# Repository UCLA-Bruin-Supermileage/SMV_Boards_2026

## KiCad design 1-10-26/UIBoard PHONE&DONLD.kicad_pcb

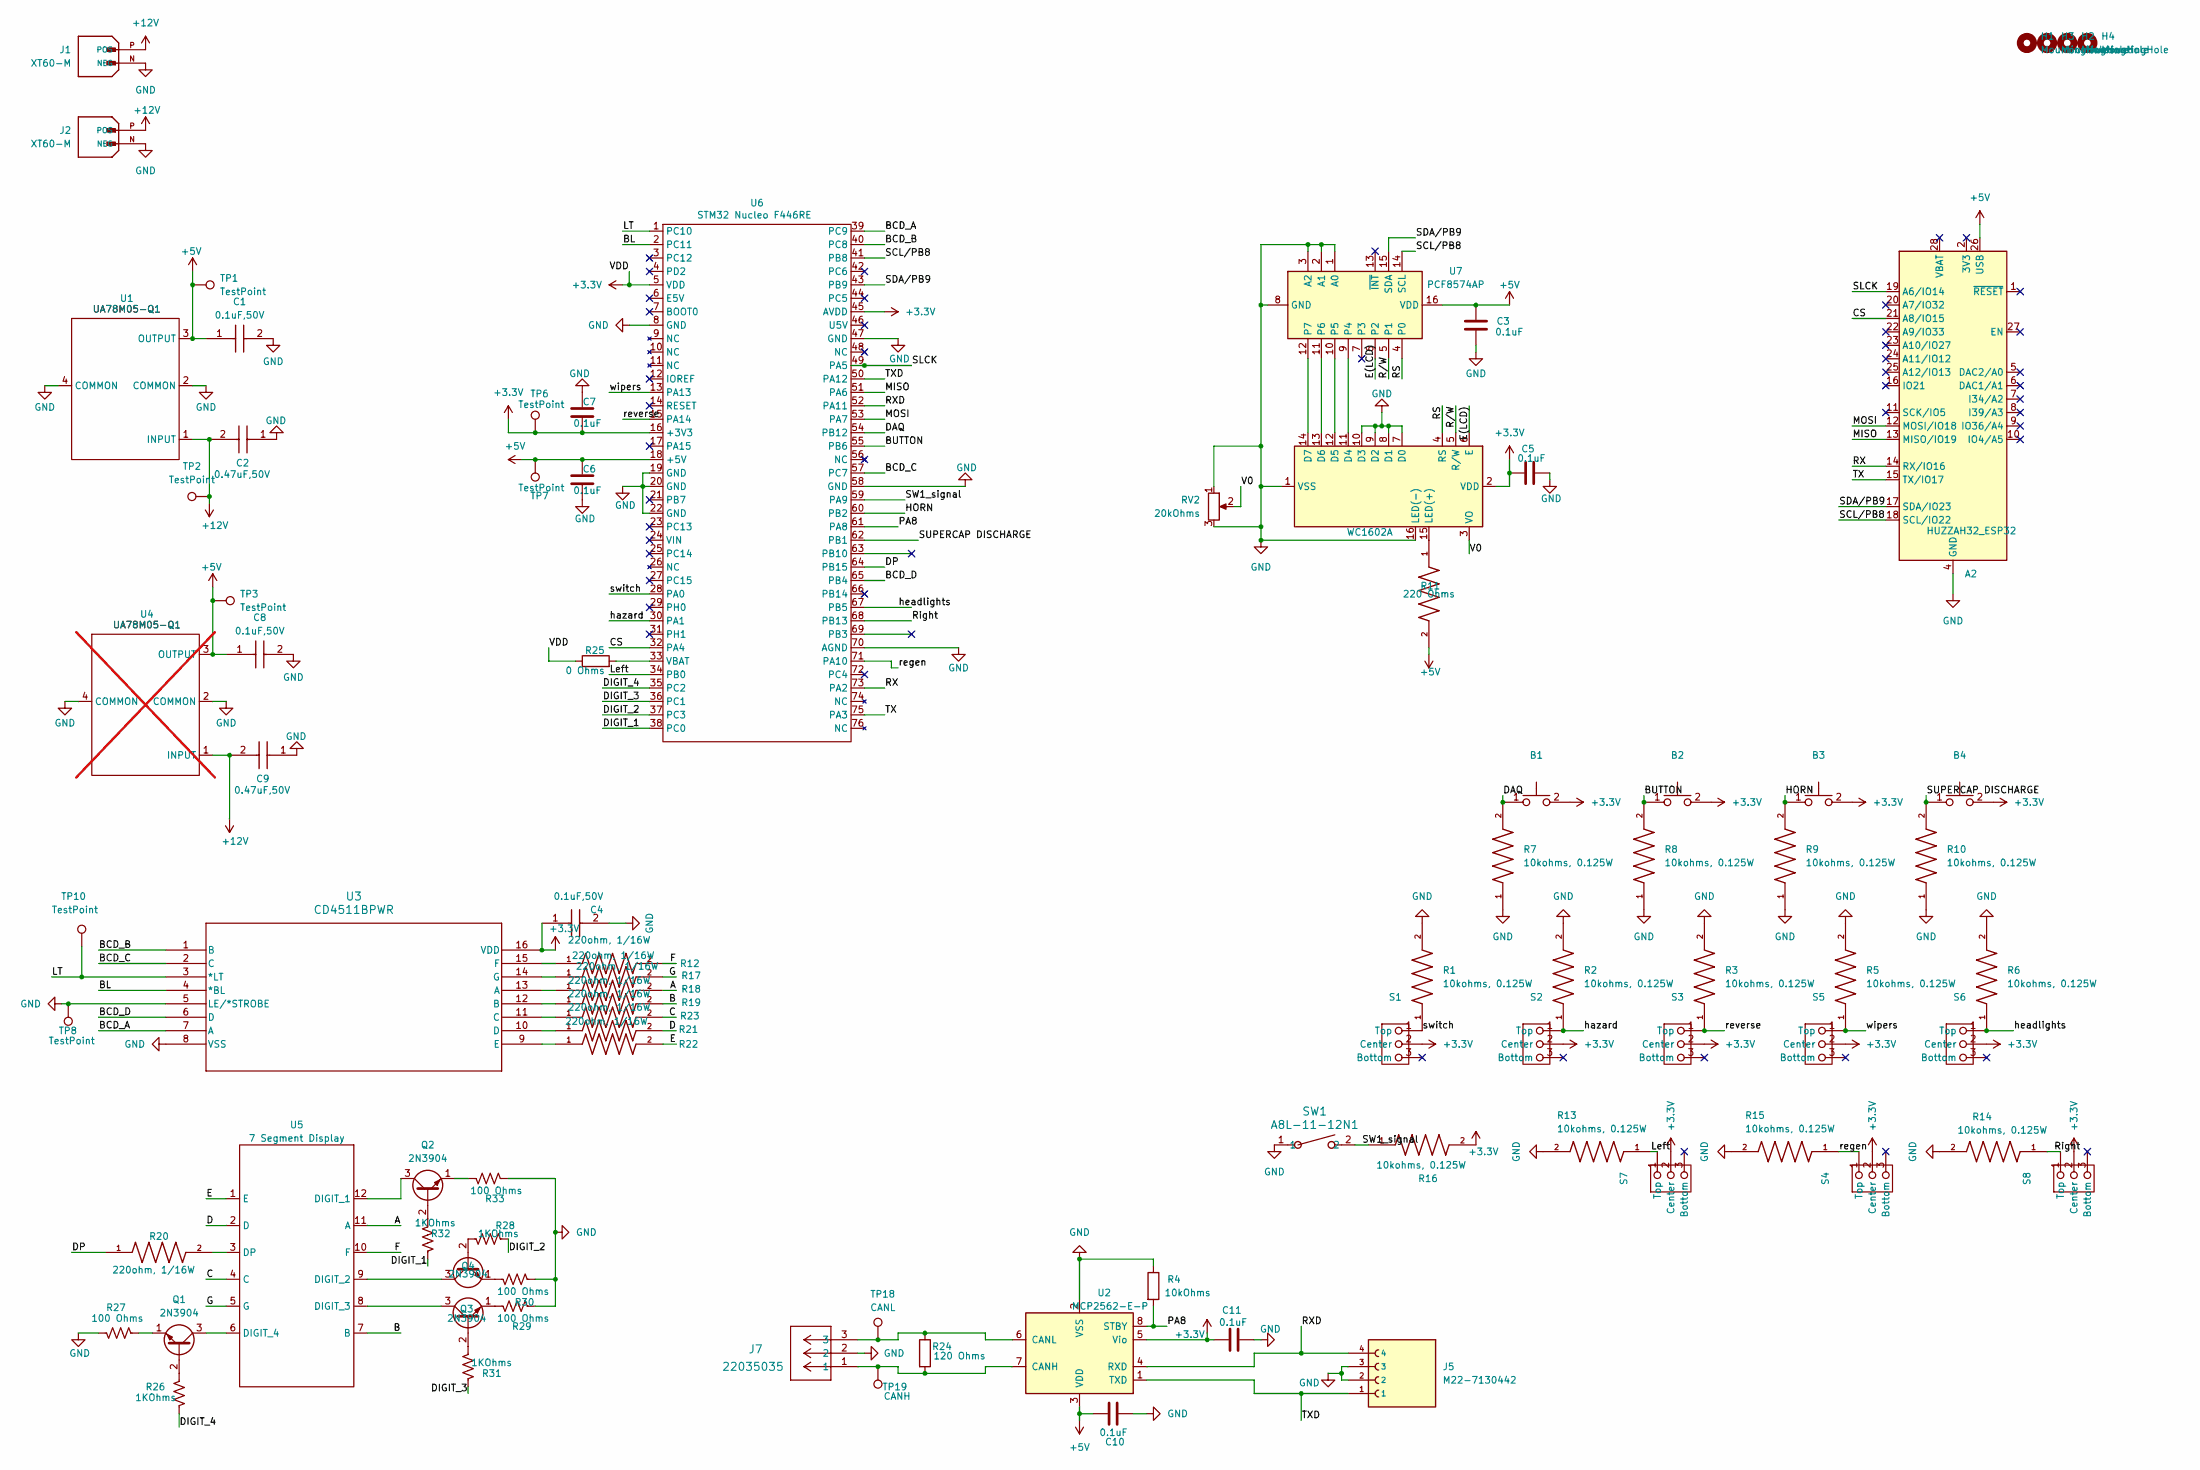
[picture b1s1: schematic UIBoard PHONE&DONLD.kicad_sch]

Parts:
A2: HUZZAH32_ESP32; Adafruit_Feather
B1, B2, B3, B4: Twidec Button
C1, C4, C8: 0.1uF,50V; Cap0805; Manufacturer_Part_Number C0805C104K5RACTU; Mouser Part Number 80-C0805C104K5R
C2, C9: 0.47uF,50V; Cap0805; Manufacturer_Part_Number C0805C334K5RACTU; Mouser Part Number 80-C0805C334K5R
C3, C5, C6, C7, C10, C11: 0.1uF; Cap0805
DS1: WC1602A
H1, H2, H3, H4: MountingHole; MountingHole_3.2mm_M3
J1, J2: XT60-M; AMASS_XT60-M; PARTREV V1.2
J5: M22-7130442; HARWIN_M22-7130442
J7: 22035035; 3pin_CON_22035035_MOL
Q1, Q2, Q3, Q4: 2N3904; TO-92_Inline
R1, R2, R3, R5, R6, R7, R8, R9, R10, R13, R14, R15, R16: 10kohms, 0.125W; 0805RESC2012X60N
R4: 10kOhms; 0805RESC2012X60N
R11: 220 Ohms; 0805RESC2012X60N
R12, R17, R18, R19, R20, R21, R22, R23: 220ohm, 1/16W; 0805RESC2012X60N
R24: 120 Ohms; 0805RESC2012X60N
R25: 0 Ohms; 0805RESC2012X60N
R26, R28, R31, R32: 1KOhms; 0805RESC2012X60N
R27, R29, R30, R33: 100 Ohms; 0805RESC2012X60N
RV2: 20kOhms; Potentiometer_ACP_CA6-VSMD_Vertical
S1, S2, S3, S4, S5, S6, S7, S8: TAISS 3 Pin Switch
SW1: A8L-11-12N1; SW_A8L-11_OMR
TP1, TP2, TP3, TP6, TP7, TP8, TP10: TestPoint; TestPoint_Pad_2.5x2.5mm
TP18: CANL; TestPoint_Pad_D1.0mm
TP19: CANH; TestPoint_Pad_D1.0mm
U1: UA78M05-Q1; SOT230P700X180-4N
U2: MCP2562-E-P; DIP-8_W7.62mm
U3: CD4511BPWR
U4: UA78M05-Q1; SOT230P700X180-4N; not fitted
U5: 7 Segment Display; Seven_Seg_display
U6: STM32 Nucleo F446RE; MODULE_NUCLEO-F446RE
U7: PCF8574AP; DIP-16_W7.62mm

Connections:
+3.3V: B1.2, B2.2, B3.2, B4.2, C4.1, C5.1, C7.2, C11.1, DS1.2 (VDD), R16.2, R25.1, S1.2 (Center), S2.2 (Center), S3.2 (Center), S4.2 (Center), S5.2 (Center), S6.2 (Center), S7.2 (Center), S8.2 (Center), TP6.1, U2.5 (Vio), U3.16 (VDD), U6.5 (VDD), U6.16 (+3V3), U6.45 (AVDD)
+5V: A2.26 (USB), C1.1, C3.1, C6.1, C8.1, C10.1, R11.2, TP1.1, TP3.1, TP7.1, U1.3 (OUTPUT), U2.3 (VDD), U4.3 (OUTPUT), U6.18 (+5V), U7.16 (VDD)
+12V: C2.2, C9.2, J1.P (POS), J2.P (POS), TP2.1, U1.1 (INPUT), U4.1 (INPUT)
/A: R18.2, U5.11 (A)
/B: R19.2, U5.7 (B)
/BCD_A: U3.7 (A), U6.39 (PC9)
/BCD_B: U3.1 (B), U6.40 (PC8)
/BCD_C: U3.2 (C), U6.57 (PC7)
/BCD_D: U3.6 (D), U6.65 (PB4)
/BL: U3.4 (*BL), U6.2 (PC11)
/BUTTON: B2.1, R8.2, U6.55 (PB6)
/C: R23.2, U5.4 (C)
/CS: A2.21 (A8/IO15), U6.32 (PA4)
/D: R21.2, U5.2 (D)
/DAQ: B1.1, R7.2, U6.54 (PB12)
/DIGIT_1: R32.1, U6.38 (PC0)
/DIGIT_2: R28.1, U6.37 (PC3)
/DIGIT_3: R31.1, U6.36 (PC1)
/DIGIT_4: R26.2, U6.35 (PC2)
/DP: R20.1, U6.64 (PB15)
/E: R22.2, U5.1 (E)
/E(LCD): DS1.6 (E), U7.6 (P2)
/F: R12.2, U5.10 (F)
/G: R17.2, U5.5 (G)
/HORN: B3.1, R9.2, U6.60 (PB2)
/LT: TP10.1, U3.3 (*LT), U6.1 (PC10)
/Left: R13.1, S7.1 (Top), U6.34 (PB0)
/MISO: A2.13 (MISO/IO19), U6.51 (PA6)
/MOSI: A2.12 (MOSI/IO18), U6.53 (PA7)
/PA8: R4.2, U2.8 (STBY), U6.61 (PA8)
/RS: DS1.4 (RS), U7.4 (P0)
/RX: A2.14 (RX/IO16), U6.73 (PA2)
/RXD: J5.4, U2.4 (RXD), U6.52 (PA11)
/Right: R14.1, S8.1 (Top), U6.68 (PB13)
/R/W: DS1.5 (R/W), U7.5 (P1)
/SCL/PB8: A2.18 (SCL/IO22), U6.41 (PB8), U7.14 (SCL)
/SDA/PB9: A2.17 (SDA/IO23), U6.43 (PB9), U7.15 (SDA)
/SLCK: A2.19 (A6/IO14), U6.49 (PA5)
/SUPERCAP DISCHARGE: B4.1, R10.2, U6.62 (PB1)
/SW1_signal: R16.1, SW1.2, U6.59 (PA9)
/TX: A2.15 (TX/IO17), U6.75 (PA3)
/TXD: J5.1, U2.1 (TXD), U6.50 (PA12)
/V0: DS1.3 (VO), RV2.2
/hazard: R2.1, S2.1 (Top), U6.30 (PA1)
/headlights: R6.1, S6.1 (Top), U6.67 (PB5)
/regen: R15.1, S4.1 (Top), U6.71 (PA10)
/reverse: R3.1, S3.1 (Top), U6.15 (PA14)
/switch: R1.1, S1.1 (Top), U6.28 (PA0)
/wipers: R5.1, S5.1 (Top), U6.13 (PA13)
GND: A2.4 (GND), C1.2, C2.1, C3.2, C4.2, C5.2, C6.2, C7.1, C8.2, C9.1, C10.2, C11.2, DS1.1 (VSS), DS1.7 (D0), DS1.8 (D1), DS1.9 (D2), DS1.10 (D3), DS1.16 (LED(-)), J1.N (NEG), J2.N (NEG), J5.2, J5.3, J7.2, R1.2, R2.2, R3.2, R4.1, R5.2, R6.2, R7.1, R8.1, R9.1, R10.1, R13.2, R14.2, R15.2, R27.2, R29.2, R30.2, R33.2, RV2.1, RV2.3, SW1.1, TP8.1, U1.2 (COMMON), U1.4 (COMMON), U2.2 (VSS), U3.5 (LE/*STROBE), U3.8 (VSS), U4.2 (COMMON), U4.4 (COMMON), U6.8 (GND), U6.19 (GND), U6.20 (GND), U6.22 (GND), U6.47 (GND), U6.58 (GND), U6.70 (AGND), U7.1 (A0), U7.2 (A1), U7.3 (A2), U7.8 (GND)
unnamed: DS1.11 (D4), U7.9 (P4)
unnamed: DS1.12 (D5), U7.10 (P5)
unnamed: DS1.13 (D6), U7.11 (P6)
unnamed: DS1.14 (D7), U7.12 (P7)
unnamed: DS1.15 (LED(+)), R11.1
unnamed: Q1.2 (B), R26.1
unnamed: Q1.3 (C), U5.6 (DIGIT_4)
unnamed: Q1.1 (E), R27.1
unnamed: Q2.2 (B), R32.2
unnamed: Q2.3 (C), U5.12 (DIGIT_1)
unnamed: Q2.1 (E), R33.1
unnamed: Q3.2 (B), R31.2
unnamed: Q3.3 (C), U5.8 (DIGIT_3)
unnamed: Q3.1 (E), R29.1
unnamed: Q4.2 (B), R28.2
unnamed: Q4.3 (C), U5.9 (DIGIT_2)
unnamed: Q4.1 (E), R30.1
unnamed: R18.1, U3.13 (A)
unnamed: R19.1, U3.12 (B)
unnamed: R21.1, U3.10 (D)
unnamed: R23.1, U3.11 (C)
unnamed: J7.1, R24.2, TP19.1, U2.7 (CANH)
unnamed: J7.3, R24.1, TP18.1, U2.6 (CANL)
unnamed: R22.1, U3.9 (E)
unnamed: R12.1, U3.15 (F)
unnamed: R17.1, U3.14 (G)
unnamed: R20.2, U5.3 (DP)
unnamed: R25.2, U6.33 (VBAT)

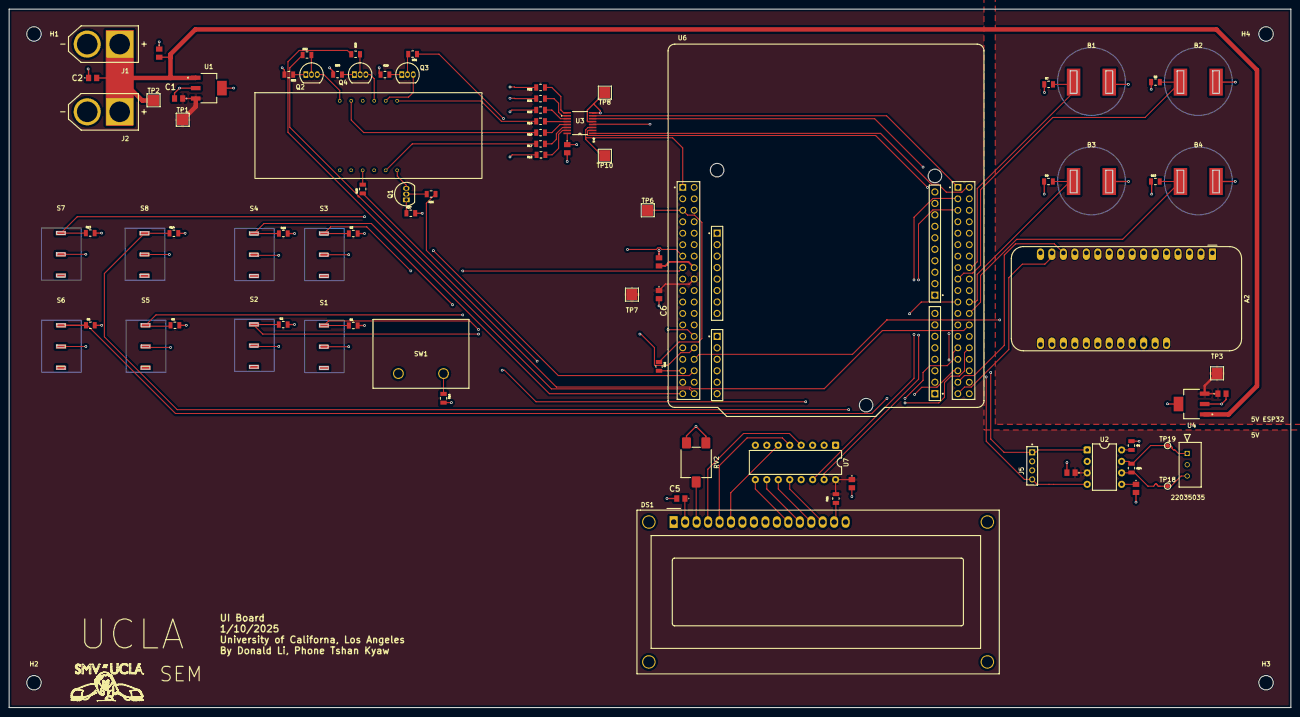
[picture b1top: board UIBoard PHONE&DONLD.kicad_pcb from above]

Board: 4 copper layers, 284.0 x 154.8 mm, 88 parts (0 on the bottom side), 78 nets.

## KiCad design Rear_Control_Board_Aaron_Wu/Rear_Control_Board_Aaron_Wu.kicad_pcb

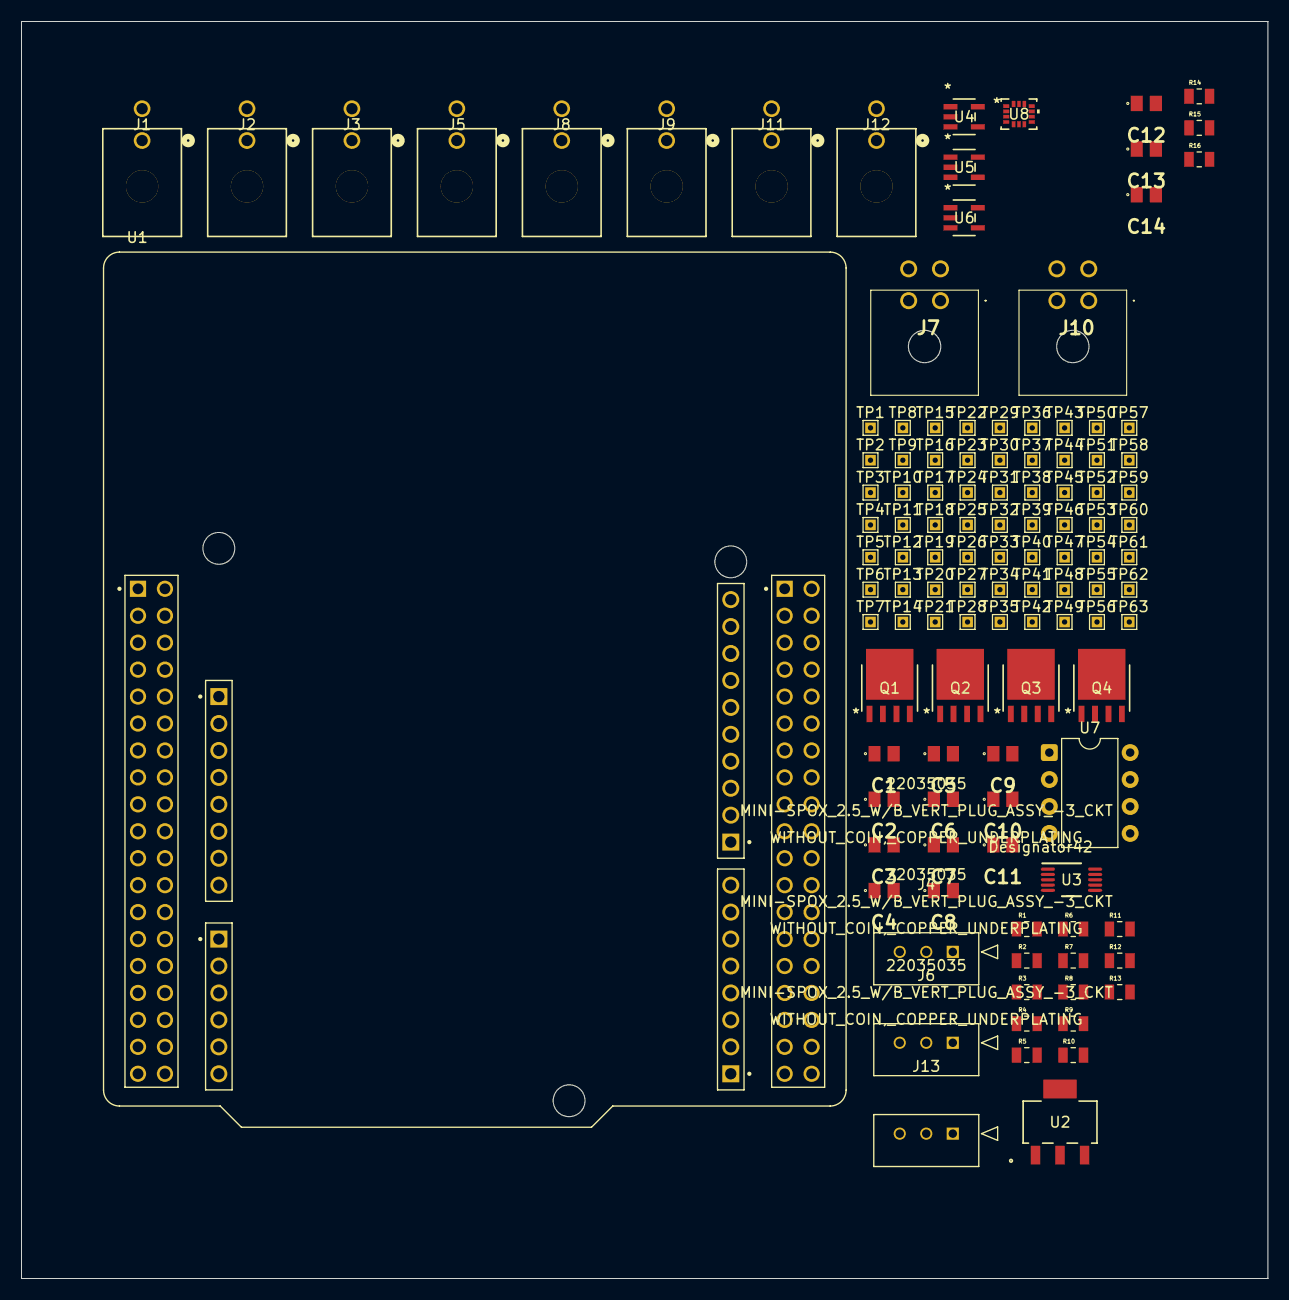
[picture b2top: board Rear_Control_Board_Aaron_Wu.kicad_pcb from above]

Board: 4 copper layers, 117.5 x 118.5 mm, 118 parts (0 on the bottom side), 32 nets, no tracks yet.

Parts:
C1, C2, C3, C4, C5, C6, C7, C8, C9, C10, C11, C12, C13, C14: 0.1uF,50V; Cap0805
J1, J2, J3, J5, J8, J9, J11, J12: 430450200; CONN_SD-43045-001_02_MOL
J4, J6, J13: 22035035; 3pin_CON_22035035_MOL
J7, J10: Molex Micro-Fit 4 Pin; 4_pin0430450401
Q1, Q2, Q3, Q4: PSMN1R8-40YLC_115; LFPAK56_SOT669_NEX
R1, R2, R5, R8, R11, R12, R13, R14, R15, R16: 100k; 0805RESC2012X60N
R3, R4, R6, R7: 100; 0805RESC2012X60N
R9: 33; 0805RESC2012X60N
R10: 10k; 0805RESC2012X60N
TP1, TP2, TP3, TP4, TP5, TP6, TP7, TP8, TP9, TP10, TP11, TP12, TP13, TP14, TP15, TP16, TP17, TP18, TP19, TP20, TP21, TP22, TP23, TP24, TP25, TP26, TP27, TP28, TP29, TP30, TP31, TP32, TP33, TP34, TP35, TP36, TP37, TP38, TP39, TP40, TP41, TP42, TP43, TP44, TP45, TP46, TP47, TP48, TP49, TP50, TP51, TP52, TP53, TP54, TP55, TP56, TP57, TP58, TP59, TP60, TP61, TP62, TP63: TestPoint; TestPoint_THTPad_1.0x1.0mm_Drill0.5mm
U1: MODULE_NUCLEO-F446RE
U2: UA78M05QDCYRG4Q1; DCY4_TEX
U3: ADS1118QDGSRQ1; DGS0010A_N
U4, U5, U6: MCP6286T-E/OT; SOT-23-5_MC_MCH
U7: MCP2562-E-P; DIP-8_W7.62mm
U8: ASM330LHHTR; LGA-14L_2P5X3X0P83_STM

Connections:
+3.3V: C4.1, C11.1, TP34.1, TP36.1, U5.5 (VDD), U7.5 (Vio)
+3V3: C3.1, C5.1, C6.1, C9.2, C10.2, R9.2, R10.1, TP10.1, TP32.1, TP45.1, TP46.1, TP47.1, U3.8 (VDD), U4.5 (VDD), U6.5 (VDD), U8.5 (VDD_IO), U8.8 (VDD)
+5V: C1.2, J6.1, TP31.1, TP35.1, TP44.1, U2.1 (OUTPUT), U7.3 (VDD)
+12V: C2.2, C7.1, C8.1, J1.1, J2.1, J3.1, J5.1, J7.3, J8.1, J9.1, J10.3, J11.1, J12.1, TP42.1, TP43.1, TP49.1, TP50.1, TP51.1, TP60.1, TP62.1, U2.3 (INPUT)
/CAN_N net: J4.3, J13.3, U7.6 (CANL)
/CAN_P net: J4.1, J13.1, U7.7 (CANH)
/CS_PA4: TP55.1, U3.2 (CS_N)
/MISO: TP56.1, U3.9 (DOUT_DRDY_N), U8.1 (SDO/SA0)
/MOSI: TP57.1, U3.10 (DIN), U8.14 (SDA)
/PB_8: TP59.1, U7.4 (RXD)
/PB_9: TP58.1, U7.1 (TXD)
/SCLK: TP16.1, TP53.1, U3.1 (SCLK), U8.13 (SCL)
GND: C1.1, C2.1, C3.2, C4.2, C5.2, C6.2, C7.2, C8.2, C9.1, C10.1, C11.2, C12.2, C13.2, C14.2, J4.2, J6.3, J7.4, J10.4, J11.2, J12.2, J13.2, Q1.1 (Source), Q1.2 (Source), Q1.3 (Source), Q2.1 (Source), Q2.2 (Source), Q2.3 (Source), Q3.1 (Source), Q3.2 (Source), Q3.3 (Source), Q4.1 (Source), Q4.2 (Source), Q4.3 (Source), R1.2, R2.2, R5.2, R8.2, TP1.1, TP2.1, TP3.1, TP4.1, TP5.1, TP6.1, TP7.1, TP8.1, TP9.1, TP11.1, TP12.1, TP13.1, TP14.1, TP15.1, TP17.1, TP18.1, TP19.1, TP20.1, TP21.1, TP22.1, TP23.1, TP33.1, TP37.1, TP38.1, TP39.1, TP40.1, TP41.1, TP52.1, TP54.1, TP61.1, TP63.1, U2.2 (GND), U2.4 (GND), U3.3 (GND), U4.2 (VSS), U5.2 (VSS), U6.2 (VSS), U7.2 (VSS), U7.8 (STBY), U8.6 (GND), U8.7 (GND)
unnamed: J6.2, R13.1, TP30.1
unnamed: J7.2, R11.1, TP28.1
unnamed: J10.2, R12.1, TP29.1
unnamed: J3.2, J5.2, Q1.5 (Drain)
unnamed: Q1.4 (Gate), R2.1, R3.1, TP24.1
unnamed: J2.2, J9.2, Q2.5 (Drain)
unnamed: Q2.4 (Gate), R1.1, R4.1, TP25.1
unnamed: J8.2, Q3.5 (Drain)
unnamed: Q3.4 (Gate), R5.1, R6.2, TP26.1
unnamed: J1.2, Q4.5 (Drain)
unnamed: Q4.4 (Gate), R7.2, R8.1, TP27.1
unnamed: R9.1, U8.3 (RES)
unnamed: R10.2, U8.2 (RES)
unnamed: R13.2, U4.3 (VIN+)
unnamed: C14.1, R16.1, U4.1 (VOUT), U4.4 (VIN-)
unnamed: R11.2, U5.3 (VIN+)
unnamed: C12.1, R14.1, U5.1 (VOUT), U5.4 (VIN-)
unnamed: R12.2, U6.3 (VIN+)
unnamed: C13.1, R15.1, U6.1 (VOUT), U6.4 (VIN-)

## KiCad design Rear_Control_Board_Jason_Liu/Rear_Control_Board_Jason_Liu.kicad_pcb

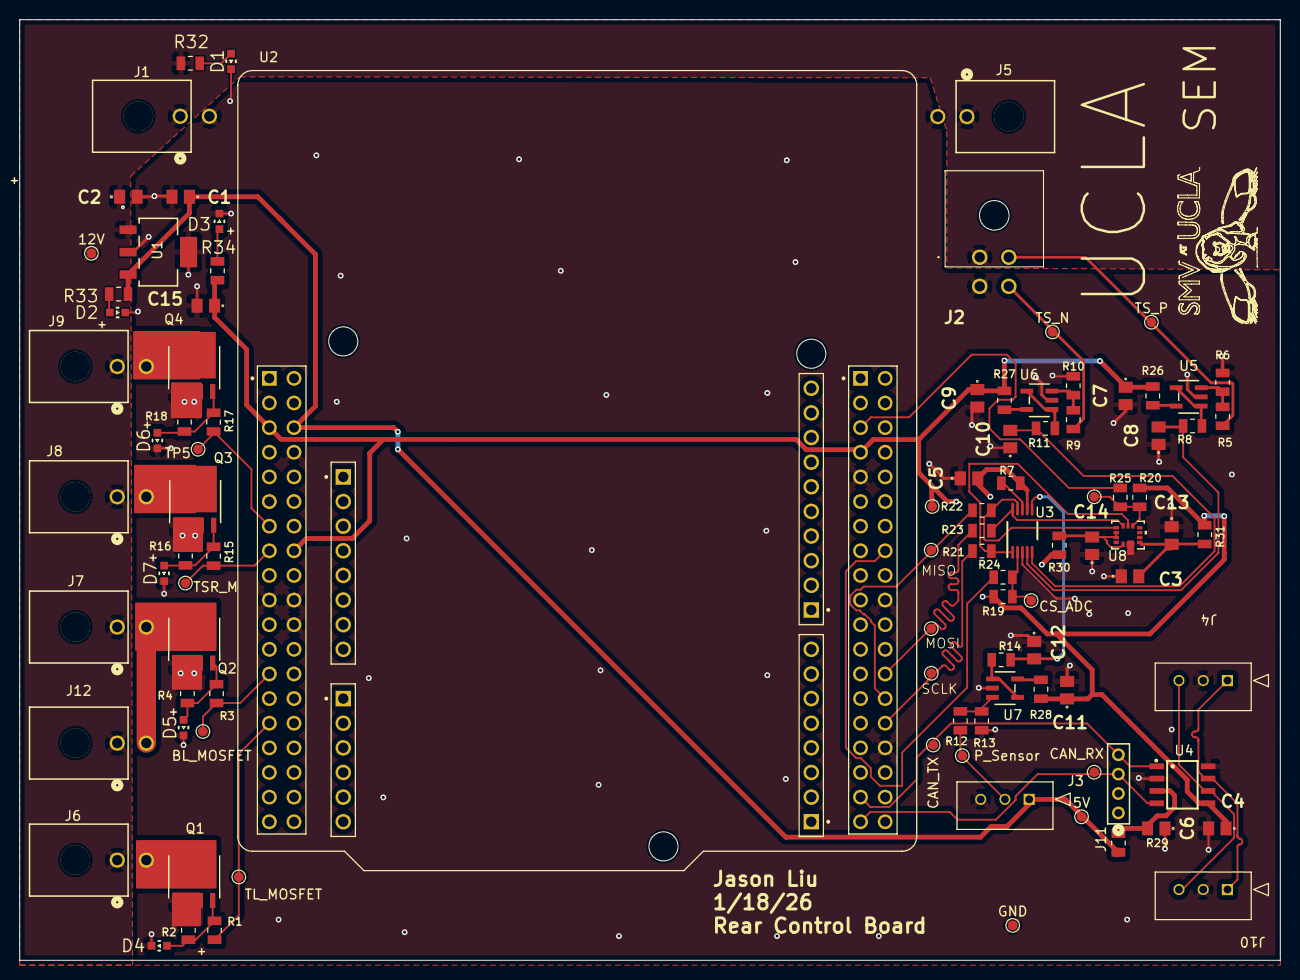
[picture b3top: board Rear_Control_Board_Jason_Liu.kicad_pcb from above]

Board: 2 copper layers, 130.0 x 97.0 mm, 98 parts (0 on the bottom side), 52 nets.

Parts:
5V: 5V1; TestPoint_Pad_D1.0mm
12V: 12V1; TestPoint_Pad_D1.0mm
BL_MOSFET: MOSFET2; TestPoint_Pad_D1.0mm
C1, C3, C4, C5, C6, C7, C9, C11, C14, C15: 0.1uF,50V; Cap0805
C2: 0.33uF,50V; Cap0805
C8, C10, C12: 4.7uF,16V; Cap0805
C13: 10nF; Cap0805
CAN_RX: CAN_RX; TestPoint_Pad_D1.0mm
CAN_TX: CAN_TX; TestPoint_Pad_D1.0mm
CS_ADC: ADC_CS; TestPoint_Pad_D1.0mm
D1, D2, D3, D4, D5, D6, D7: WL-SMCW_0603; WL-SMCW_0603(diode)
GND: 5V1; TestPoint_Pad_D1.0mm
J1, J5, J6, J7, J8, J9, J12: 430450200; CONN_SD-43045-001_02_MOL
J2: Molex Micro-Fit 4 Pin; 4_pin0430450401
J3: 22035035; 3pin_CON_22035035_MOL
J4: Low-Power Jouelmeter; 3pin_CON_22035035_MOL
J10: Front-Control Board; 3pin_CON_22035035_MOL
J11: M22-7130442; M22-7130442_TYC
P_Sensor: P_Sensor; TestPoint_Pad_D1.0mm
Q1, Q2, Q3, Q4: PSMN1R8-40YLC_115; LFPAK56_SOT669_NEX
R1, R3, R15, R17: 1KΩ; 0805RESC2012X60N
R2, R4, R12, R13, R16, R18, R19, R20, R32, R33, R34: 10kohms, 0.125W; 0805RESC2012X60N
R5, R9: 47k Ohms; 0805RESC2012X60N
R6, R10: 12.1k Ohms; 0805RESC2012X60N
R7, R26, R27, R28, R29, R30, R31: 0 Ohm; 0805RESC2012X60N
R8, R11, R14, R21, R22, R23, R24, R25: 50Ω; 0805RESC2012X60N
TL_MOSFET: MOSFET1; TestPoint_Pad_D1.0mm
TP2: 3.3V1; TestPoint_Pad_D1.0mm
TP5: MOSFET3; TestPoint_Pad_D1.0mm
TP20: SCLK; TestPoint_Pad_D1.0mm
TP21: MISO; TestPoint_Pad_D1.0mm
TP22: MOSI; TestPoint_Pad_D1.0mm
TP23: Acc_CS; TestPoint_Pad_D1.0mm
TSR_M: MOSFET4; TestPoint_Pad_D1.0mm
TS_N: T_Sensor_N; TestPoint_Pad_D1.0mm
TS_P: T_Sensor_P; TestPoint_Pad_D1.0mm
U1: UA78M05QDCYRG4Q1; DCY4_TEX
U2: MODULE_NUCLEO-F446RE
U3: ADS1118QDGSRQ1; DGS0010A_N
U4: MCP2562-E/P; SOIC127P600X175-8N
U5, U6, U7: MCP6286T-E/OT; SOT-23-5_MC_MCH
U8: ASM330LHHTR; LGA-14L_2P5X3X0P83_STM

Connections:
+3.3V: C4.1, C5.2, C7.1, C9.1, C11.1, C15.1, R7.2, R19.2, R20.2, R26.2, R27.2, R28.2, R30.2, R31.1, R34.2, TP2.1, U2.CN7_5 (VDD), U2.CN7_16 (+3V3), U2.CN10_7 (AVDD), U3.7 (AIN3), U4.5 (VIO)
+5V: 5V.1, C1.1, J3.1, R29.2, R33.1, U1.3 (OUTPUT), U2.CN7_6 (E5V)
+12V: 12V.1, C2.1, J1.1, J2.1, J5.1, J6.1, J7.1, J8.1, J9.1, J12.1, R32.2, U1.1 (INPUT)
/BL_MOSFET: BL_MOSFET.1, R3.1, U2.CN7_25 (PC14)
/CAN_N: J4.3, J10.3, U4.6 (CANL)
/CAN_P: J4.1, J10.1, U4.7 (CANH)
/CAN_RX: CAN_RX.1, J11.3, U2.CN10_37 (PA3), U4.4 (RXD)
/CAN_TX: CAN_TX.1, J11.4, U2.CN10_35 (PA2), U4.1 (TXD)
/CS_ADC: R24.1, U2.CN10_16 (PB12)
/CS_Acc: R25.1, U2.CN10_5 (PB9)
/MISO: R22.1, U3.9 (DOUT_DRDY_N), U8.1 (SDO/SA0)
/MOSI: R23.1, U3.10 (DIN), U8.14 (SDA)
/P_Sensor: J3.2, P_Sensor.1, R12.2
/P_Sensor_ADC: C12.2, R14.1, U3.6 (AIN2)
/SCLK: R21.1, U3.1 (SCLK), U8.13 (SCL)
/TL_MOSFET: R1.1, TL_MOSFET.1, U2.CN7_29 (PH0)
/TSL_MOSFET: R17.1, TP5.1, U2.CN7_13 (PA13)
/TSR_MOSFET: R15.1, TSR_M.1, U2.CN7_15 (PA14)
/T_Sensor_ADC_N: C10.2, R11.1, U3.5 (AIN1)
/T_Sensor_ADC_P: C8.2, R8.1, U3.4 (AIN0)
/T_Sensor_N: J2.4, R9.2, TS_N.1
/T_Sensor_P: J2.2, R5.2, TS_P.1
GND: C1.2, C2.2, C3.1, C4.2, C5.1, C6.1, C7.2, C8.1, C9.2, C10.1, C11.2, C12.1, C13.1, C14.1, C15.2, D1.1, D2.1, D3.1, D4.1, D5.1, D6.1, D7.1, GND.1, J1.2, J2.3, J3.3, J4.2, J5.2, J10.2, Q1.1, Q1.2, Q1.3, Q2.1, Q2.2, Q2.3, Q3.1, Q3.2, Q3.3, Q4.1, Q4.2, Q4.3, R2.2, R4.2, R6.1, R10.1, R13.1, R16.2, R18.2, U1.2 (GND), U1.4 (GND), U2.CN7_8 (GND), U2.CN7_19 (GND), U2.CN7_20 (GND), U2.CN7_22 (GND), U2.CN10_9 (GND), U2.CN10_20 (GND), U2.CN10_32 (AGND), U3.3 (GND), U4.2 (VSS), U4.8 (STBY), U5.2 (VSS), U6.2 (VSS), U7.2 (VSS), U8.6 (GND), U8.7 (GND)
unnamed: D1.2, R32.1
unnamed: D2.2, R33.2
unnamed: D3.2, R34.1
unnamed: D4.2, Q1.4, R1.2, R2.1
unnamed: D5.2, Q2.4, R3.2, R4.1
unnamed: D6.2, Q4.4, R17.2, R18.1
unnamed: D7.2, Q3.4, R15.2, R16.1
unnamed: J6.2, Q1.5
unnamed: J8.2, Q3.5
unnamed: J9.2, Q4.5
unnamed: J7.2, J12.2, Q2.5
unnamed: R21.2, TP20.1, U2.CN10_30 (PB13)
unnamed: R22.2, TP21.1, U2.CN10_28 (PB14)
unnamed: R23.2, TP22.1, U2.CN10_26 (PB15)
unnamed: CS_ADC.1, R19.1, R24.2, U3.2 (CS_N)
unnamed: R7.1, U3.8 (VDD)
unnamed: C6.2, R29.1, U4.3 (VDD)
unnamed: R26.1, U5.5 (VDD)
unnamed: R5.1, R6.2, U5.3 (VIN+)
unnamed: R8.2, U5.1 (VOUT), U5.4 (VIN-)
unnamed: R27.1, U6.5 (VDD)
unnamed: R9.1, R10.2, U6.3 (VIN+)
unnamed: R11.2, U6.1 (VOUT), U6.4 (VIN-)
unnamed: R28.1, U7.5 (VDD)
unnamed: R12.1, R13.2, U7.3 (VIN+)
unnamed: R14.2, U7.1 (VOUT), U7.4 (VIN-)
unnamed: R20.1, R25.2, TP23.1, U8.12 (CS)
unnamed: C3.2, C13.2, R31.2, U8.8 (VDD)
unnamed: C14.2, R30.1, U8.2 (RES), U8.3 (RES), U8.5 (VDD_IO)

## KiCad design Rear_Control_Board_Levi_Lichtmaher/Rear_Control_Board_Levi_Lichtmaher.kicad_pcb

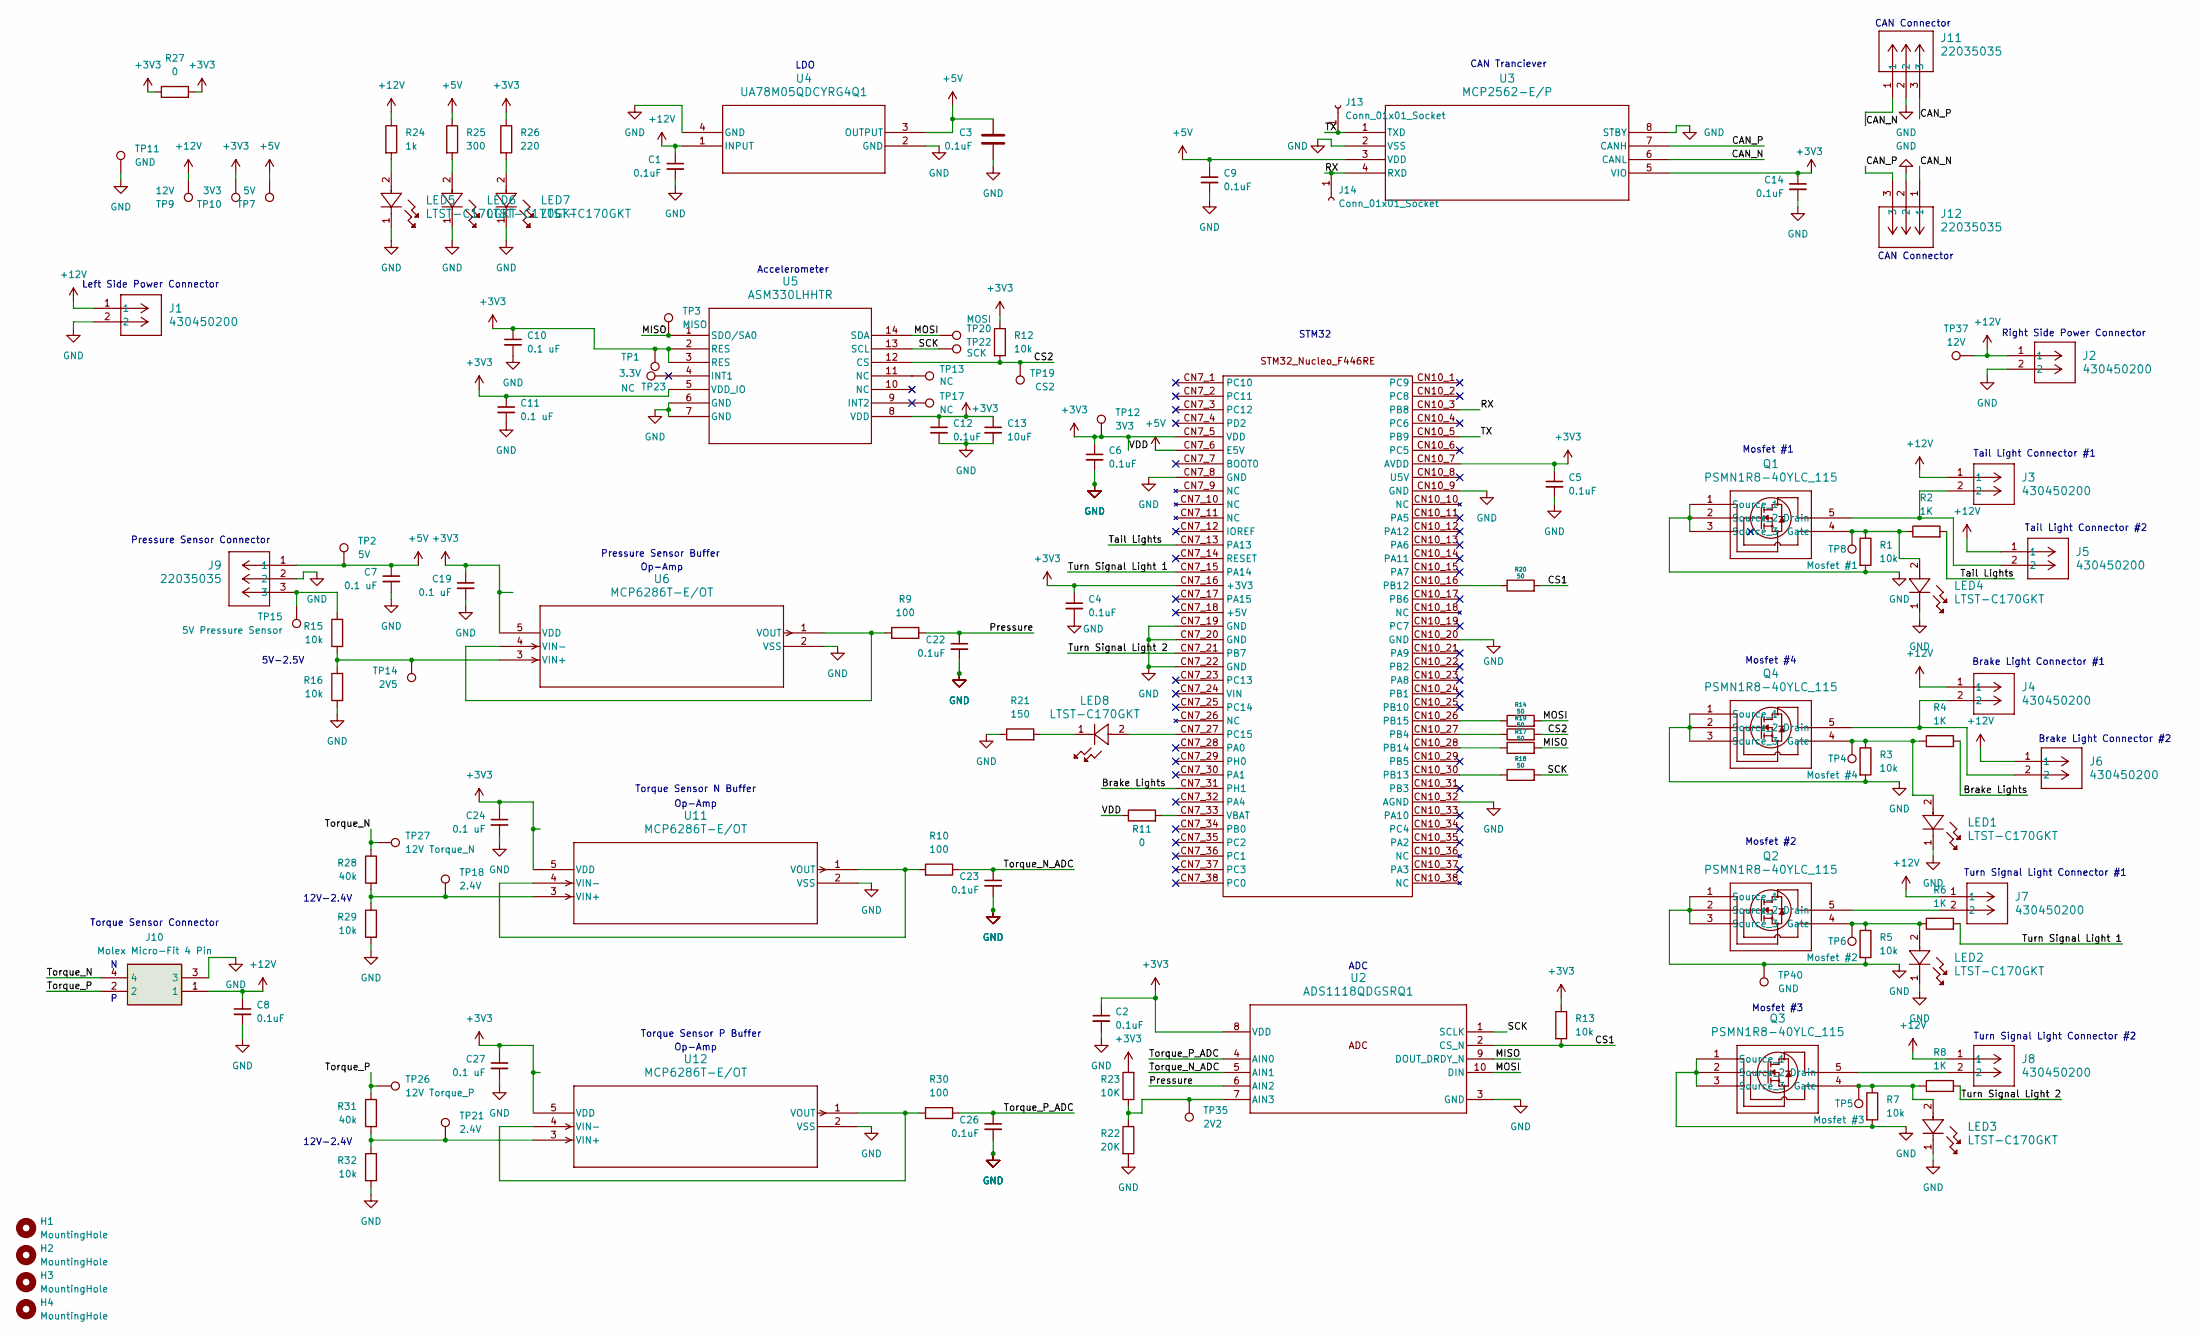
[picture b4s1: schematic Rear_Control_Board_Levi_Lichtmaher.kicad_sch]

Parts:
C1, C2, C3, C4, C5, C6, C8, C9, C12, C14, C22, C23, C26: 0.1uF; C_0805_2012Metric
C7, C10, C11, C19, C24, C27: 0.1 uF; C_0805_2012Metric
C13: 10uF; C_0805_2012Metric
H1, H2, H3, H4: MountingHole; MountingHole_3.2mm_M3
J1, J2, J3, J4, J5, J6, J7, J8: 430450200; CONN_SD-43045-001_02_MOL
J9, J11, J12: 22035035; 3pin_CON_22035035_MOL
J10: Molex Micro-Fit 4 Pin; 4_pin0430450401; Manufacturer_Part_Number 0430450401
J13, J14: Conn_01x01_Socket; PinSocket_1x01_P2.54mm_Vertical
LED1, LED2, LED3, LED4, LED5, LED6, LED7, LED8: LTST-C170GKT; LED_LTST-C170GKT_LTO
Q1, Q2, Q3, Q4: PSMN1R8-40YLC_115; LFPAK56_SOT669_NEX-mosfet
R1, R3, R5, R7, R12, R13, R15, R16, R29, R32: 10k; R_0805_2012Metric
R2, R4, R6, R8: 1K; R_0805_2012Metric
R9, R10, R30: 100; R_0805_2012Metric
R11, R27: 0; R_0805_2012Metric
R14, R17, R18, R19, R20: 50; R_0805_2012Metric
R21: 150; R_0805_2012Metric
R22: 20K; R_0805_2012Metric
R23: 10K; R_0805_2012Metric
R24: 1k; R_0805_2012Metric
R25: 300; R_0805_2012Metric
R26: 220; R_0805_2012Metric
R28, R31: 40k; R_0805_2012Metric
TP1: 3.3V; TestPoint_Pad_D1.0mm
TP2: 5V; TestPoint_Pad_D1.0mm
TP3: MISO; TestPoint_Pad_D1.0mm
TP4: Mosfet #4; TestPoint_Pad_D1.0mm
TP5: Mosfet #3; TestPoint_Pad_D1.0mm
TP6: Mosfet #2; TestPoint_Pad_D1.0mm
TP7: 5V; TestPoint_Plated_Hole_D2.0mm
TP8: Mosfet #1; TestPoint_Pad_D1.0mm
TP9: 12V; TestPoint_Plated_Hole_D2.0mm
TP10: 3V3; TestPoint_Plated_Hole_D2.0mm
TP11: GND; TestPoint_Plated_Hole_D2.0mm
TP12: 3V3; TestPoint_Pad_D1.0mm
TP13, TP17, TP23: NC; TestPoint_Pad_D1.0mm
TP14: 2V5; TestPoint_Pad_D1.0mm
TP15: 5V Pressure Sensor; TestPoint_Pad_D1.0mm
TP18, TP21: 2.4V; TestPoint_Pad_D1.0mm
TP19: CS2; TestPoint_Pad_D1.0mm
TP20: MOSI; TestPoint_Pad_D1.0mm
TP22: SCK; TestPoint_Pad_D1.0mm
TP26: 12V Torque_P; TestPoint_Pad_D1.0mm
TP27: 12V Torque_N; TestPoint_Pad_D1.0mm
TP35: 2V2; TestPoint_Pad_D1.0mm
TP37: 12V; TestPoint_Pad_D1.0mm
TP40: GND; TestPoint_Pad_D1.0mm
U2: ADS1118QDGSRQ1; DGS0010A_N
U3: MCP2562-E/P; SOIC127P600X175-8N
U4: UA78M05QDCYRG4Q1; DCY4_TEX
U5: ASM330LHHTR; QFN_LHHXTR_STM
U6, U11, U12: MCP6286T-E/OT; SOT-23-5_MC_MCH
U7: MODULE_NUCLEO-F446RE

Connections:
+3V3: C2.1, C4.1, C5.1, C6.1, C10.1, C11.1, C12.1, C13.1, C14.1, C19.1, C24.1, C27.1, R11.1, R12.1, R13.1, R23.2, R26.1, R27.1, R27.2, TP1.1, TP10.1, TP12.1, U2.8 (VDD), U3.5 (VIO), U5.2 (RES), U5.3 (RES), U5.5 (VDD_IO), U5.8 (VDD), U6.5 (VDD), U7.CN7_5 (VDD), U7.CN7_16 (+3V3), U7.CN10_7 (AVDD), U11.5 (VDD), U12.5 (VDD)
+5V: C3.1, C7.1, C9.1, J9.1, R25.1, TP2.1, TP7.1, U3.3 (VDD), U4.3 (OUTPUT), U7.CN7_6 (E5V)
+12V: C1.1, C8.1, J1.1, J2.1, J3.1, J4.1, J5.1, J6.1, J7.1, J8.1, J10.1, R24.1, TP9.1, TP37.1, U4.1 (INPUT)
/Brake Lights: R4.2, U7.CN7_31 (PH1)
/CAN_N: J11.1, J12.1, U3.6 (CANL)
/CAN_P: J11.3, J12.3, U3.7 (CANH)
/CS1: R13.2, R20.2, U2.2 (CS_N)
/CS2: R12.2, R19.2, TP19.1, U5.12 (CS)
/MISO: R17.2, TP3.1, U2.9 (DOUT_DRDY_N), U5.1 (SDO/SA0)
/MOSI: R14.2, TP20.1, U2.10 (DIN), U5.14 (SDA)
/Pressure: C22.1, R9.1, U2.6 (AIN2)
/RX: J14.1, U3.4 (RXD), U7.CN10_3 (PB8)
/SCK: R18.2, TP22.1, U2.1 (SCLK), U5.13 (SCL)
/TX: J13.1, U3.1 (TXD), U7.CN10_5 (PB9)
/Tail Lights: R2.2, U7.CN7_13 (PA13)
/Torque_N: J10.4, R28.1, TP27.1
/Torque_N_ADC: C23.1, R10.1, U2.5 (AIN1)
/Torque_P: J10.2, R31.1, TP26.1
/Torque_P_ADC: C26.1, R30.1, U2.4 (AIN0)
/Turn Signal Light 1: R6.2, U7.CN7_15 (PA14)
/Turn Signal Light 2: R8.2, U7.CN7_21 (PB7)
GND: C1.2, C2.2, C3.2, C4.2, C5.2, C6.2, C7.2, C8.2, C9.2, C10.2, C11.2, C12.2, C13.2, C14.2, C19.2, C22.2, C23.2, C24.2, C26.2, C27.2, J1.2, J2.2, J9.2, J10.3, J11.2, J12.2, LED1.1, LED2.1, LED3.1, LED4.1, LED5.1, LED6.1, LED7.1, Q1.1 (Source_1), Q1.2 (Source_2), Q1.3 (Source_3), Q2.1 (Source_1), Q2.2 (Source_2), Q2.3 (Source_3), Q3.1 (Source_1), Q3.2 (Source_2), Q3.3 (Source_3), Q4.1 (Source_1), Q4.2 (Source_2), Q4.3 (Source_3), R1.2, R3.2, R5.2, R7.2, R16.2, R21.1, R22.2, R29.2, R32.2, TP11.1, TP40.1, U2.3 (GND), U3.2 (VSS), U3.8 (STBY), U4.2 (GND), U4.4 (GND), U5.6 (GND), U5.7 (GND), U6.2 (VSS), U7.CN7_8 (GND), U7.CN7_19 (GND), U7.CN7_20 (GND), U7.CN7_22 (GND), U7.CN10_9 (GND), U7.CN10_20 (GND), U7.CN10_32 (AGND), U11.2 (VSS), U12.2 (VSS)
unnamed: J9.3, R15.1, TP15.1
unnamed: LED5.2, R24.2
unnamed: LED6.2, R25.2
unnamed: LED7.2, R26.2
unnamed: LED8.1, R21.2
unnamed: J3.2, J5.2, Q1.5 (Drain)
unnamed: LED4.2, Q1.4 (Gate), R1.1, R2.1, TP8.1
unnamed: J7.2, Q2.5 (Drain)
unnamed: LED2.2, Q2.4 (Gate), R5.1, R6.1, TP6.1
unnamed: J8.2, Q3.5 (Drain)
unnamed: LED3.2, Q3.4 (Gate), R7.1, R8.1, TP5.1
unnamed: J4.2, J6.2, Q4.5 (Drain)
unnamed: LED1.2, Q4.4 (Gate), R3.1, R4.1, TP4.1
unnamed: TP13.1, U5.11 (NC)
unnamed: R22.1, R23.1, TP35.1, U2.7 (AIN3)
unnamed: R15.2, R16.1, TP14.1, U6.3 (VIN+)
unnamed: R9.2, U6.1 (VOUT), U6.4 (VIN-)
unnamed: R19.1, U7.CN10_27 (PB4)
unnamed: R20.1, U7.CN10_16 (PB12)
unnamed: R18.1, U7.CN10_30 (PB13)
unnamed: R17.1, U7.CN10_28 (PB14)
unnamed: R14.1, U7.CN10_26 (PB15)
unnamed: LED8.2, U7.CN7_27 (PC15)
unnamed: R11.2, U7.CN7_33 (VBAT)
unnamed: R28.2, R29.1, TP18.1, U11.3 (VIN+)
unnamed: R10.2, U11.1 (VOUT), U11.4 (VIN-)
unnamed: R31.2, R32.1, TP21.1, U12.3 (VIN+)
unnamed: R30.2, U12.1 (VOUT), U12.4 (VIN-)

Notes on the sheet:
CAN Connector
Tail Light Connector #2
Torque Sensor P Buffer
Left Side Power Connector
Op-Amp
12V-2.4V
Accelerometer
Tail Light Connector #1
Turn Signal Light Connector #1
Turn Signal Light Connector #2
Pressure Sensor Connector
Mosfet #3
Mosfet #4
ADC
Pressure Sensor Buffer
STM32
Mosfet #1
LDO
Mosfet #2
5V-2.5V
Right Side Power Connector
CAN Tranciever
Brake Light Connector #2
Torque Sensor Connector
Torque Sensor N Buffer
Brake Light Connector #1
